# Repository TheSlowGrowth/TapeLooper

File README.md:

# TapeLooper

A digital tape looper module for Eurorack or standalone use, built on the [Daisy Seed](https://electro-smith.com/product/daisy-seed/).

## Features

- **4 stereo or mono tape loop channels** - record and play back independent, unsynchronized tape loops
- **Motor simulation** - playback speed ramps up and down with a configurable rate
- **Tape simulation** - with drive, grain and warble independently controllable
- **Variable playback speed** - with Volt/Octave CV control and quarter/half/double/quad speed
- **Forward and reverse playback**
- **Amplitude CV control**
- **Clean recording** — audio records cleanly into loop channels; tape simulation is applied during playback only
- **Perfect loop recording** - with a small crossfade at the loop point
- **SD card storage** - save and load loops as 48kHz stereo WAV files

## Hardware

Based on the Electrosmith Daisy Seed. Designed to operate as either a Eurorack module or a standalone desktop unit.

## Project Structure

- `dsp/` — DSP library: audio processing, loop playback/recording, tape simulation
- `firmware/` — Target firmware: main application, UI, SD card I/O
- `hardware/` — KiCad PCB designs and panel artwork
- `lib/` — External dependencies
- `scripts/` — Development helper scripts

## Development

### Requirements

- **CMake** 3.30+
- **clang++** (C++17) for building and running unit tests
- **arm-none-eabi-gcc** 10-2020-q4 recommended for cross-compiling firmware to the Daisy Seed
- **Python 3** with `pip` (for pre-commit hooks)

### Unit Tests

Tests are written with Google Test. Build and run from the respective `tests/` directories:

```bash
# DSP library tests
cd dsp/tests && make test

# Firmware tests
cd firmware/tests && make test
```

### Pre-commit Hook

A pre-commit hook runs `clang-format` on staged files before each commit. To install:

```bash
./scripts/setup-clangformat-precommit-hook.sh
```

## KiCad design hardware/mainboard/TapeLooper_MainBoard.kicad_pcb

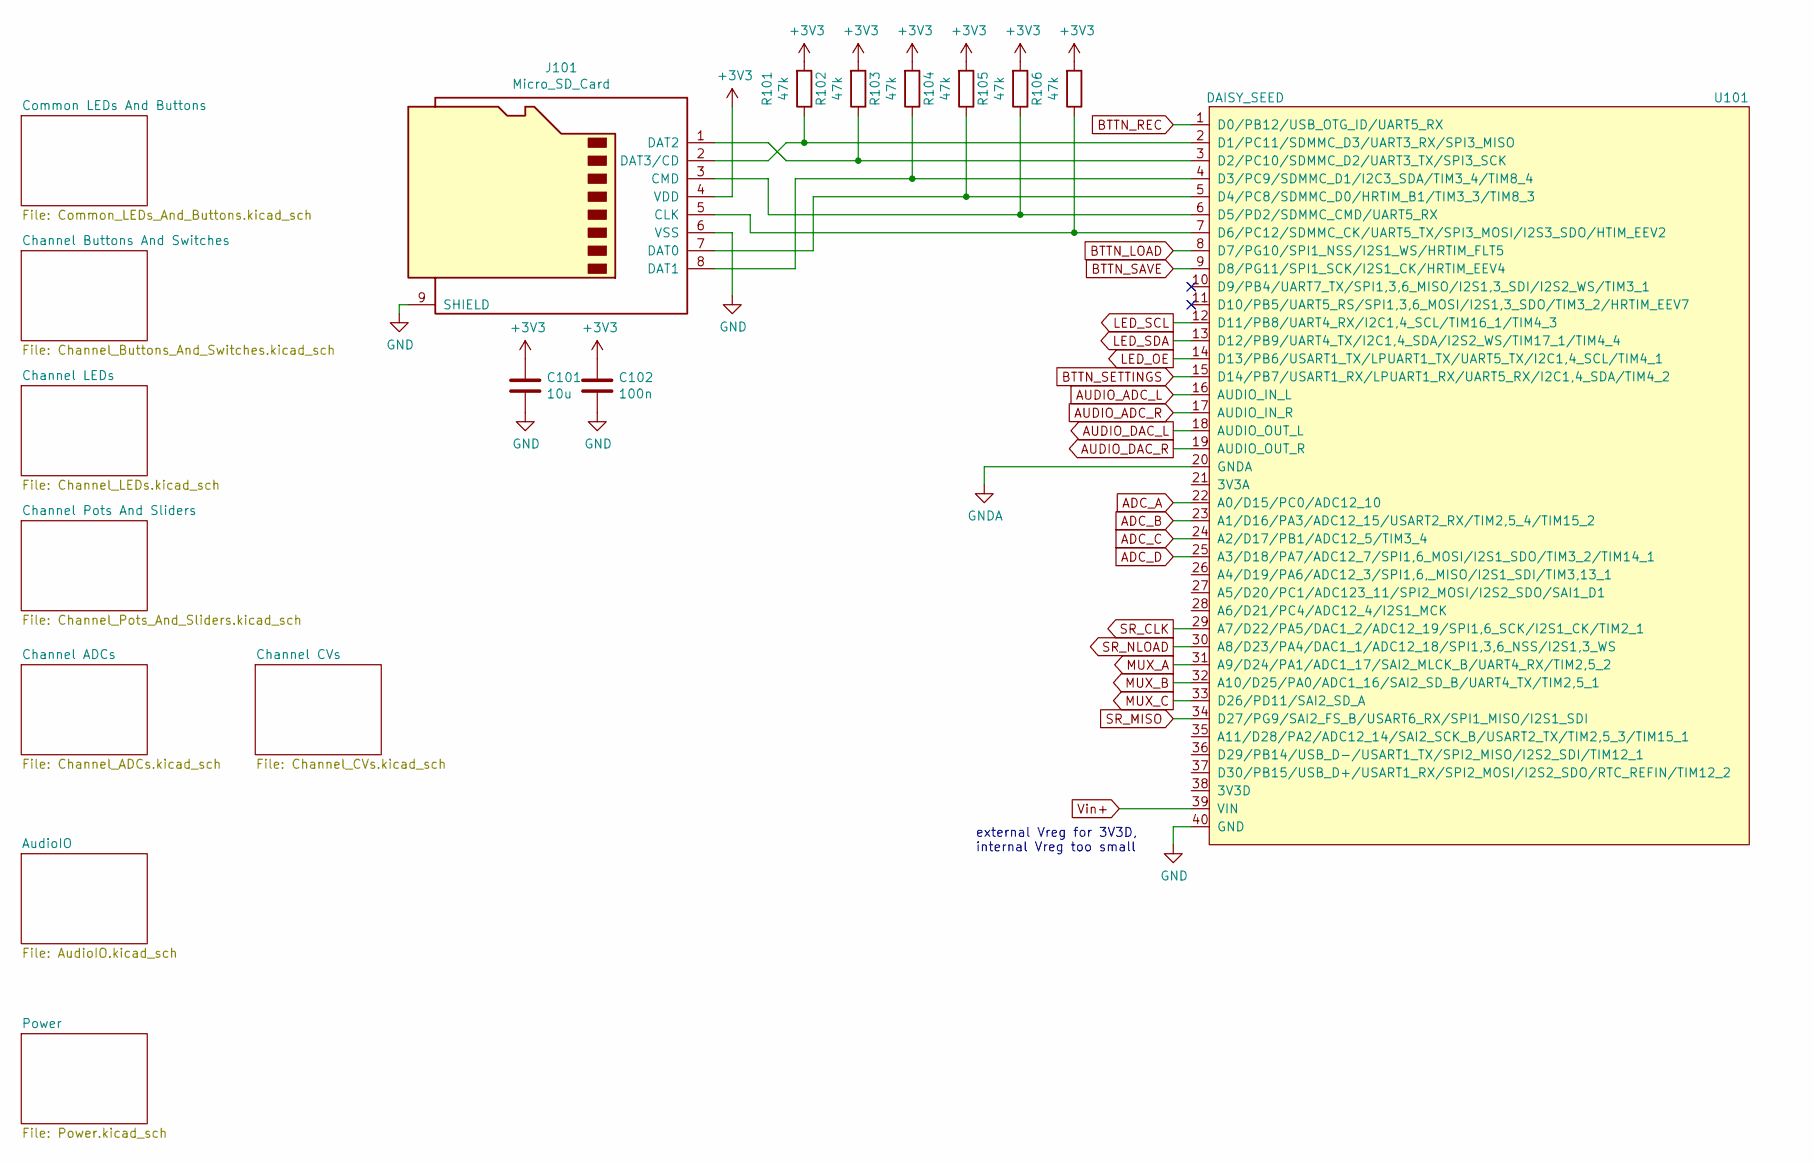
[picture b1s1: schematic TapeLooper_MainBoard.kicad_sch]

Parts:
C101: 10u; C_0603_1608Metric_Pad1.08x0.95mm_HandSolder
C102: 100n; C_0603_1608Metric_Pad1.08x0.95mm_HandSolder
J101: Micro_SD_Card; PJS008U-3000
R101, R102, R103, R104, R105, R106: 47k; R_0603_1608Metric_Pad0.98x0.95mm_HandSolder
U101: DAISY_SEED; Daisy_Seed

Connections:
ADC_A: U101.22 (A0/D15/PC0/ADC12_10); also elsewhere on the board
ADC_B: U101.23 (A1/D16/PA3/ADC12_15/USART2_RX/TIM2,5_4/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); also elsewhere on the board
ADC_C: U101.24 (A2/D17/PB1/ADC12_5/TIM3_4); also elsewhere on the board
ADC_D: U101.25 (A3/D18/PA7/ADC12_7/SPI1,6_MOSI/I2S1_SDO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); also elsewhere on the board
AUDIO_ADC_L: U101.16 (AUDIO_IN_L); also elsewhere on the board
AUDIO_ADC_R: U101.17 (AUDIO_IN_R); also elsewhere on the board
AUDIO_DAC_L: U101.18 (AUDIO_OUT_L); also elsewhere on the board
AUDIO_DAC_R: U101.19 (AUDIO_OUT_R); also elsewhere on the board
BTTN_LOAD: U101.8 (D7/PG10/SPI1_NSS/I2S1_WS/HRTIM_FLT5); also elsewhere on the board
BTTN_REC: U101.1 (D0/PB12/USB_OTG_ID/UART5_RX); also elsewhere on the board
BTTN_SAVE: U101.9 (D8/PG11/SPI1_SCK/I2S1_CK/HRTIM_EEV4); also elsewhere on the board
BTTN_SETTINGS: U101.15 (D14/PB7/USART1_RX/LPUART1_RX/UART5_RX/I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); also elsewhere on the board
GND: C101.2, C102.2, J101.6 (VSS), J101.9 (SHIELD), U101.40 (GND); also elsewhere on the board
LED_OE: U101.14 (D13/PB6/USART1_TX/LPUART1_TX/UART5_TX/I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); also elsewhere on the board
LED_SCL: U101.12 (D11/PB8/UART4_RX/I2C1,4_SCL/TIM16_1/TIM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); also elsewhere on the board
LED_SDA: U101.13 (D12/PB9/UART4_TX/I2C1,4_SDA/I2S2_WS/TIM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); also elsewhere on the board
MUX_A: U101.31 (A9/D24/PA1/ADC1_17/SAI2_MLCK_B/UART4_RX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); also elsewhere on the board
MUX_B: U101.32 (A10/D25/PA0/ADC1_16/SAI2_SD_B/UART4_TX/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); also elsewhere on the board
MUX_C: U101.33 (D26/PD11/SAI2_SD_A); also elsewhere on the board
unnamed: J101.5 (CLK), R106.1, U101.7 (D6/PC12/SDMMC_CK/UART5_TX/SPI3_MOSI/I2S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)
unnamed: J101.3 (CMD), R105.1, U101.6 (D5/PD2/SDMMC_CMD/UART5_RX)
unnamed: J101.7 (DAT0), R104.1, U101.5 (D4/PC8/SDMMC_D0/HRTIM_B1/TIM3_3/TIM8_3)
unnamed: J101.8 (DAT1), R103.1, U101.4 (D3/PC9/SDMMC_D1/I2C3_SDA/TIM3_4/TIM8_4)
unnamed: J101.1 (DAT2), R102.1, U101.3 (D2/PC10/SDMMC_D2/UART3_TX/SPI3_SCK)
unnamed: J101.2 (DAT3/CD), R101.1, U101.2 (D1/PC11/SDMMC_D3/UART3_RX/SPI3_MISO)
SR_CLK: U101.29 (A7/D22/PA5/DAC1_2/ADC12_19/SPI1,6_SCK/I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); also elsewhere on the board
SR_MISO: U101.34 (D27/PG9/SAI2_FS_B/USART6_RX/SPI1_MISO/I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); also elsewhere on the board
SR_NLOAD: U101.30 (A8/D23/PA4/DAC1_1/ADC12_18/SPI1,3,6_NSS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); also elsewhere on the board
Vin+: U101.39 (VIN); also elsewhere on the board

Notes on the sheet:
external Vreg for 3V3D, internal Vreg too small

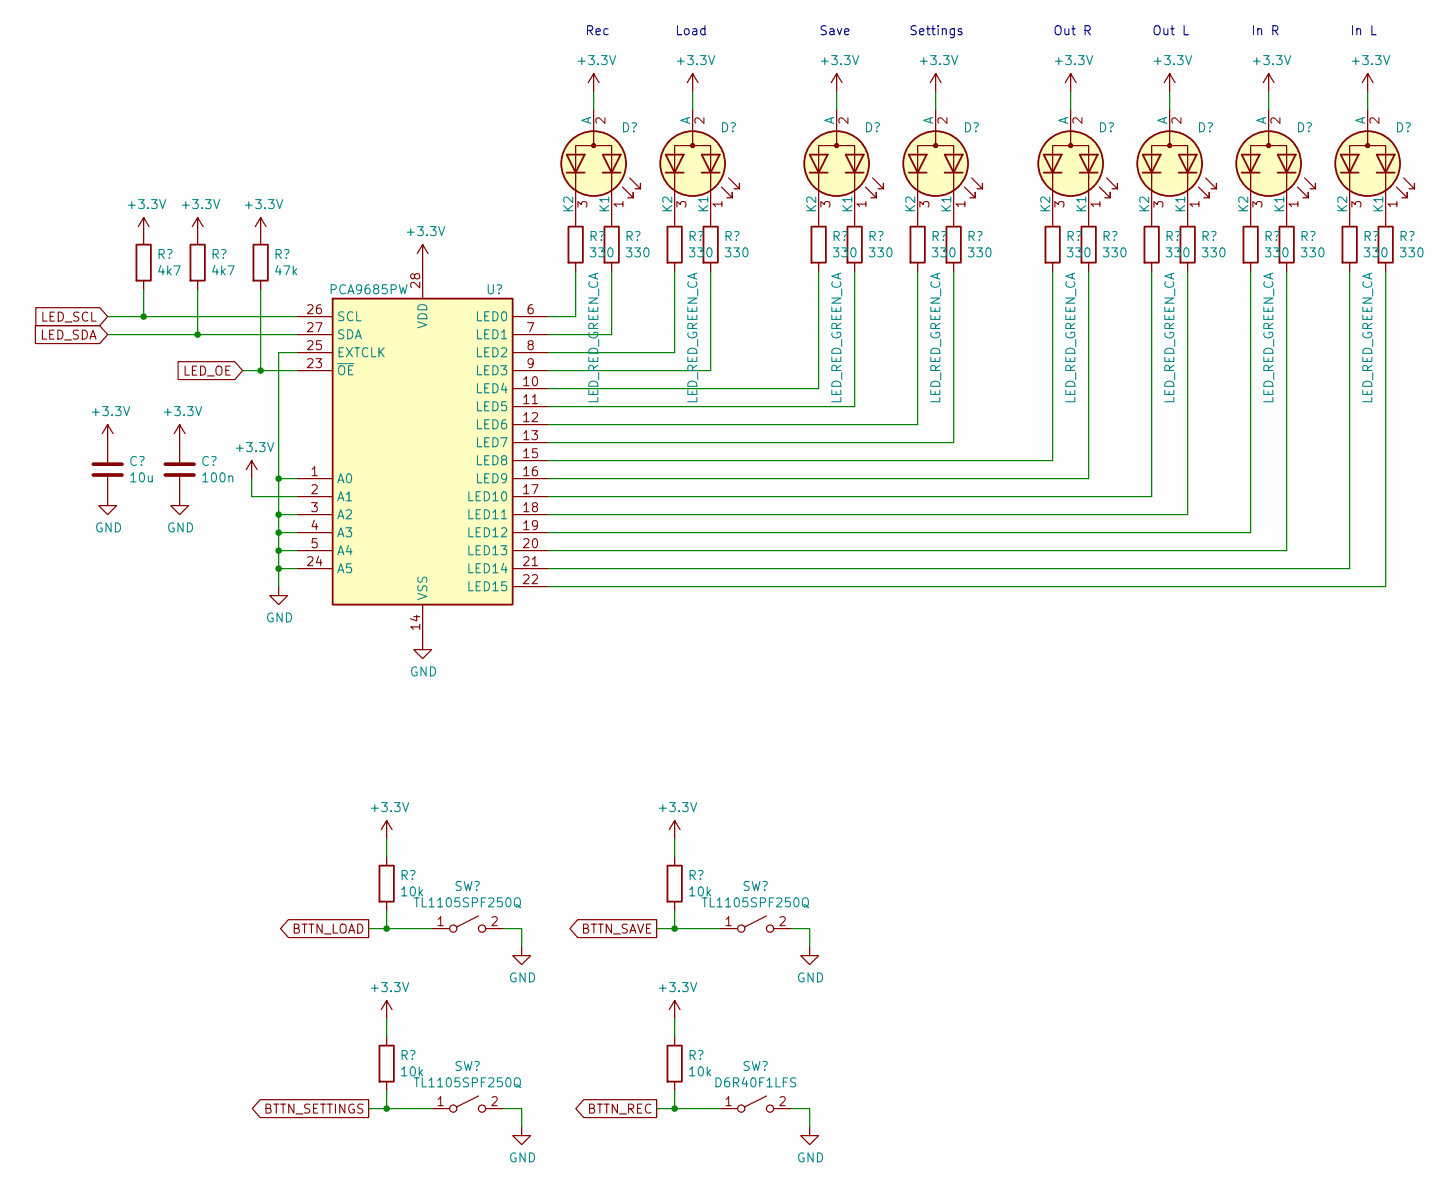
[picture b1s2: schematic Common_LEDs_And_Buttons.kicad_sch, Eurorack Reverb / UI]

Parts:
C201: 10u; C_0603_1608Metric_Pad1.08x0.95mm_HandSolder
C202: 100n; C_0603_1608Metric_Pad1.08x0.95mm_HandSolder
D201, D202, D203, D204, D205, D206, D207, D208: LED_RED_GREEN_CA; LED_D3.0mm-3
R201, R202, R203, R204, R205, R206, R207, R208, R209, R210, R211, R212, R213, R214, R215, R216: 330; R_0603_1608Metric_Pad0.98x0.95mm_HandSolder
R217, R218: 4k7; R_0603_1608Metric_Pad0.98x0.95mm_HandSolder
R219: 47k; R_0603_1608Metric_Pad0.98x0.95mm_HandSolder
R220, R221, R222, R223: 10k; R_0603_1608Metric_Pad0.98x0.95mm_HandSolder
SW201, SW202, SW203: TL1105SPF250Q; SW_PUSH_6mm
SW204: D6R40F1LFS; CK-D6R_Pushbutton
U201: PCA9685PW; TSSOP-28_4.4x9.7mm_P0.65mm

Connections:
BTTN_LOAD: R220.2, SW201.1 (A); also elsewhere on the board
BTTN_REC: R223.2, SW204.1 (A); also elsewhere on the board
BTTN_SAVE: R221.2, SW202.1 (A); also elsewhere on the board
BTTN_SETTINGS: R222.2, SW203.1 (A); also elsewhere on the board
GND: C201.2, C202.2, SW201.2 (B), SW202.2 (B), SW203.2 (B), SW204.2 (B), U201.1 (A0), U201.3 (A2), U201.4 (A3), U201.5 (A4), U201.14 (VSS), U201.24 (A5), U201.25 (EXTCLK); also elsewhere on the board
LED_OE: R219.2, U201.23 (~OE); also elsewhere on the board
LED_SCL: R217.2, U201.26 (SCL); also elsewhere on the board
LED_SDA: R218.2, U201.27 (SDA); also elsewhere on the board
unnamed: D201.1 (K1), R202.1
unnamed: D201.3 (K2), R201.1
unnamed: D202.1 (K1), R204.1
unnamed: D202.3 (K2), R203.1
unnamed: D203.1 (K1), R206.1
unnamed: D203.3 (K2), R205.1
unnamed: D204.1 (K1), R208.1
unnamed: D204.3 (K2), R207.1
unnamed: D205.1 (K1), R210.1
unnamed: D205.3 (K2), R209.1
unnamed: D206.1 (K1), R212.1
unnamed: D206.3 (K2), R211.1
unnamed: D207.1 (K1), R214.1
unnamed: D207.3 (K2), R213.1
unnamed: D208.1 (K1), R216.1
unnamed: D208.3 (K2), R215.1
unnamed: R201.2, U201.6 (LED0)
unnamed: R202.2, U201.7 (LED1)
unnamed: R203.2, U201.8 (LED2)
unnamed: R204.2, U201.9 (LED3)
unnamed: R205.2, U201.10 (LED4)
unnamed: R206.2, U201.11 (LED5)
unnamed: R207.2, U201.12 (LED6)
unnamed: R208.2, U201.13 (LED7)
unnamed: R209.2, U201.15 (LED8)
unnamed: R210.2, U201.16 (LED9)
unnamed: R211.2, U201.17 (LED10)
unnamed: R212.2, U201.18 (LED11)
unnamed: R213.2, U201.19 (LED12)
unnamed: R214.2, U201.20 (LED13)
unnamed: R215.2, U201.21 (LED14)
unnamed: R216.2, U201.22 (LED15)

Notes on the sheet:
In R
Rec
Load
Out L
In L
Settings
Save
Out R

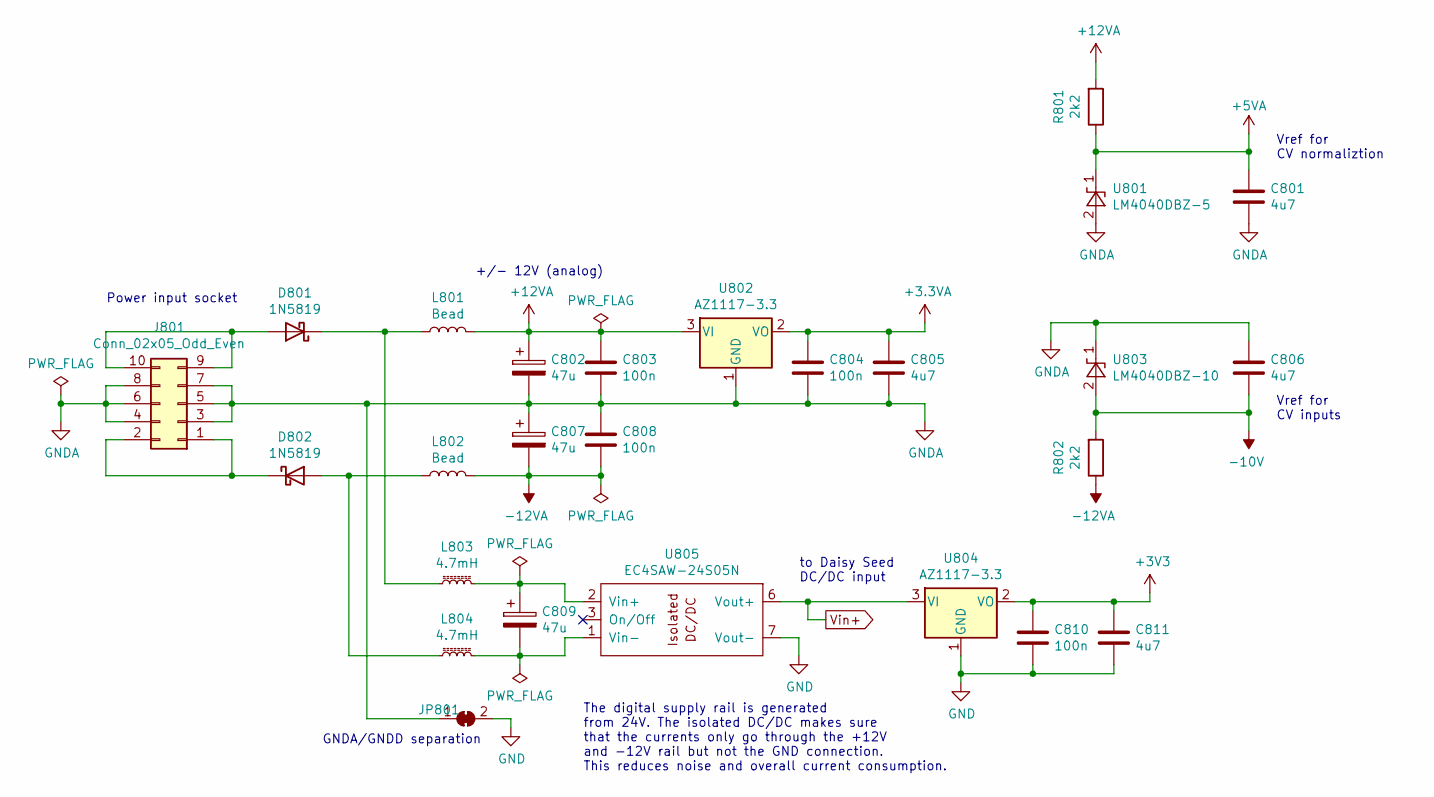
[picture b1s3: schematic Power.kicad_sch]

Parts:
C801, C805, C806, C811: 4u7; C_0603_1608Metric_Pad1.08x0.95mm_HandSolder
C802, C807, C809: 47u; CP_Elec_6.3x5.8
C803, C804, C808, C810: 100n; C_0603_1608Metric_Pad1.08x0.95mm_HandSolder
D801, D802: 1N5819; D_SOD-123
J801: Conn_02x05_Odd_Even; IDC-Header_2x05_P2.54mm_Vertical
JP801: SolderJumper_2_Bridged; SolderJumper-2_P1.3mm_Bridged2Bar_RoundedPad1.0x1.5mm
L801, L802: Bead; L_0603_1608Metric_Pad1.05x0.95mm_HandSolder
L803, L804: 4.7mH; L_1210_3225Metric_Pad1.42x2.65mm_HandSolder
R801, R802: 2k2; R_0603_1608Metric_Pad0.98x0.95mm_HandSolder
U801: LM4040DBZ-5; SOT-23
U802, U804: AZ1117-3.3; SOT-223-3_TabPin2
U803: LM4040DBZ-10; SOT-23
U805: EC4SAW-24S05N; EC4SAW_DC_DC_SIP8

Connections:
+5VA: C801.1, R801.1, U801.1 (K); also elsewhere on the board
+12VA: C802.1, C803.1, L801.2, R801.2, U802.3 (VI); also elsewhere on the board
-10V: C806.2, R802.2, U803.2 (A); also elsewhere on the board
-12VA: C807.2, C808.2, L802.2, R802.1; also elsewhere on the board
GND: C810.2, C811.2, JP801.2 (B), U804.1 (GND), U805.7 (Vout-); also elsewhere on the board
unnamed: D801.2 (A), J801.9, J801.10
unnamed: D801.1 (K), L801.1, L803.1
unnamed: D802.2 (A), L802.1, L804.1
unnamed: D802.1 (K), J801.1, J801.2
unnamed: C809.1, L803.2, U805.2 (Vin+)
unnamed: C809.2, L804.2, U805.1 (Vin-)
Vin+: U804.3 (VI), U805.6 (Vout+); also elsewhere on the board

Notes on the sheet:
GNDA/GNDD separation
to Daisy Seed DC/DC input
The digital supply rail is generated from 24V. The isolated DC/DC makes sure that the currents only go through the +12V and -12V rail but not the GND connection. This reduces noise and overall current consumption.
Power input socket
Vref for CV normaliztion
+/- 12V (analog)
Vref for CV inputs

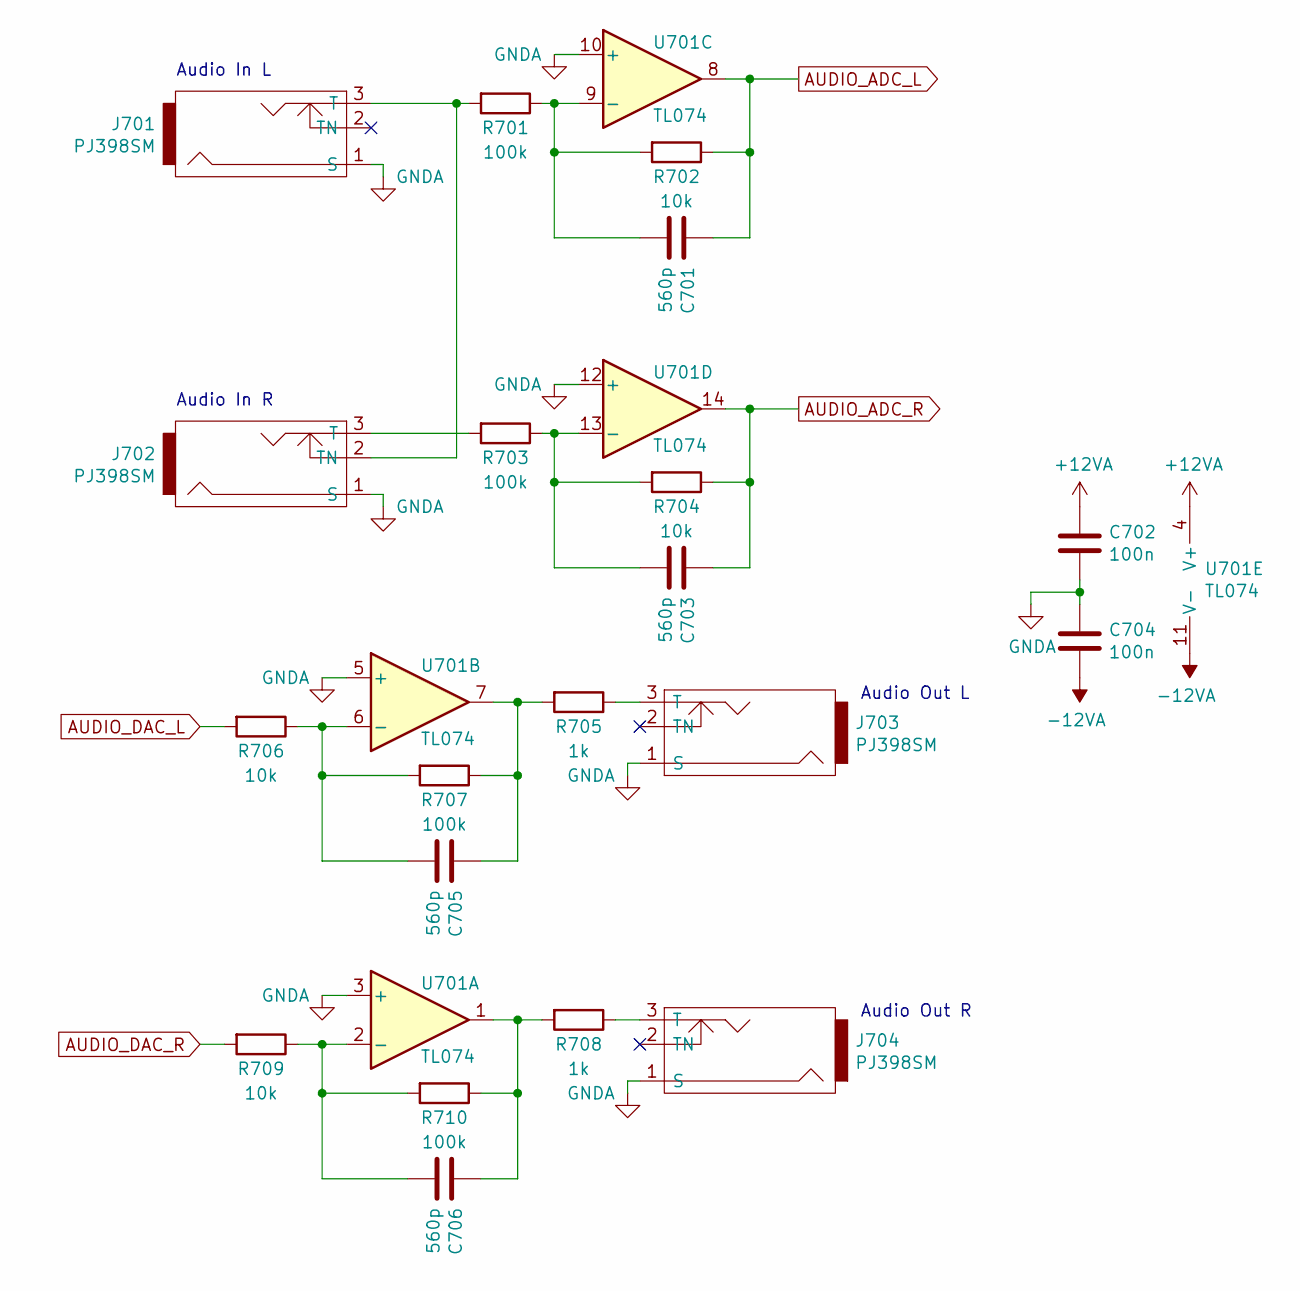
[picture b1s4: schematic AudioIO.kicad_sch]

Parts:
C701, C703, C705, C706: 560p; C_0603_1608Metric_Pad1.08x0.95mm_HandSolder
C702, C704: 100n; C_0603_1608Metric_Pad1.08x0.95mm_HandSolder
J701, J702, J703, J704: PJ398SM; THONKICONN
R701, R703, R707, R710: 100k; R_0603_1608Metric_Pad0.98x0.95mm_HandSolder
R702, R704, R706, R709: 10k; R_0603_1608Metric_Pad0.98x0.95mm_HandSolder
R705, R708: 1k; R_0603_1608Metric_Pad0.98x0.95mm_HandSolder
U701: TL074; SOIC-14_3.9x8.7mm_P1.27mm

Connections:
+12VA: C702.1, U701.4 (V+); also elsewhere on the board
-12VA: C704.2, U701.11 (V-); also elsewhere on the board
AUDIO_ADC_L: C701.1, R702.1, U701.8; also elsewhere on the board
AUDIO_ADC_R: C703.1, R704.1, U701.14; also elsewhere on the board
AUDIO_DAC_L: R706.2; also elsewhere on the board
AUDIO_DAC_R: R709.2; also elsewhere on the board
unnamed: C705.1, R705.2, R707.1, U701.7
unnamed: C706.1, R708.2, R710.1, U701.1
unnamed: J701.3 (T), J702.2 (TN), R701.2
unnamed: J702.3 (T), R703.2
unnamed: J703.3 (T), R705.1
unnamed: J704.3 (T), R708.1
unnamed: C706.2, R709.1, R710.2, U701.2 (-)
unnamed: C705.2, R706.1, R707.2, U701.6 (-)
unnamed: C701.2, R701.1, R702.2, U701.9 (-)
unnamed: C703.2, R703.1, R704.2, U701.13 (-)

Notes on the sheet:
Audio Out L
Audio In L
Audio In R
Audio Out R

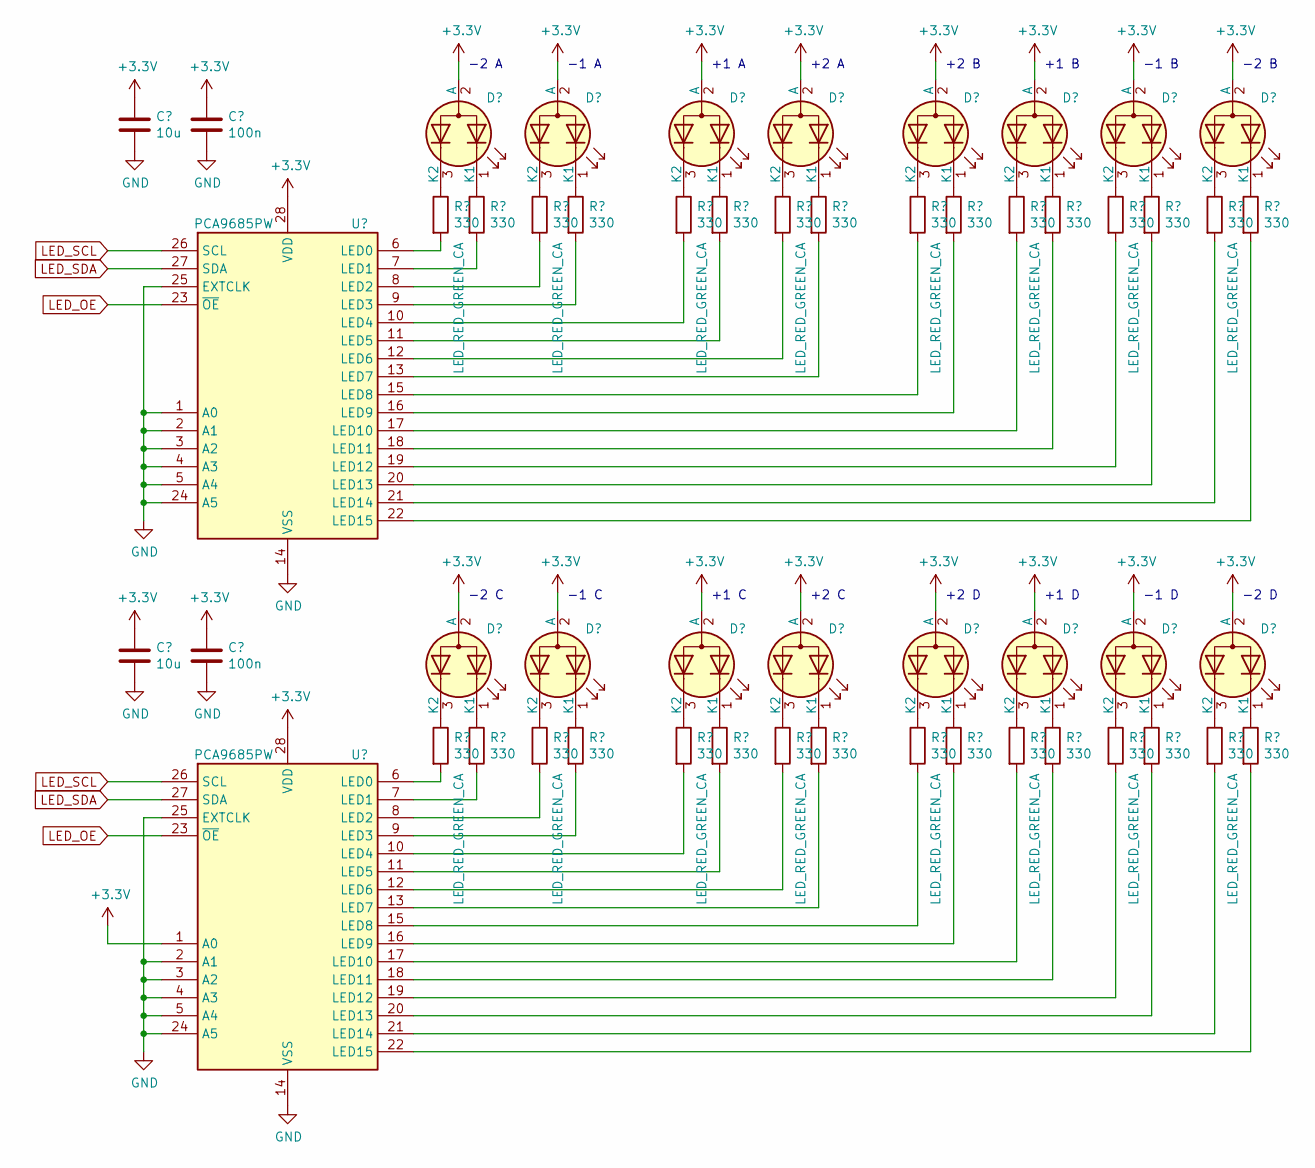
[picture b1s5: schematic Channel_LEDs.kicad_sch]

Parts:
C401, C403: 10u; C_0603_1608Metric_Pad1.08x0.95mm_HandSolder
C402, C404: 100n; C_0603_1608Metric_Pad1.08x0.95mm_HandSolder
D401, D402, D403, D404, D405, D406, D407, D408, D409, D410, D411, D412, D413, D414, D415, D416: LED_RED_GREEN_CA; LED_D3.0mm-3
R401, R402, R403, R404, R405, R406, R407, R408, R409, R410, R411, R412, R413, R414, R415, R416, R417, R418, R419, R420, R421, R422, R423, R424, R425, R426, R427, R428, R429, R430, R431, R432: 330; R_0603_1608Metric_Pad0.98x0.95mm_HandSolder
U401, U402: PCA9685PW; TSSOP-28_4.4x9.7mm_P0.65mm

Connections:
GND: C401.2, C402.2, C403.2, C404.2, U401.1 (A0), U401.2 (A1), U401.3 (A2), U401.4 (A3), U401.5 (A4), U401.14 (VSS), U401.24 (A5), U401.25 (EXTCLK), U402.2 (A1), U402.3 (A2), U402.4 (A3), U402.5 (A4), U402.14 (VSS), U402.24 (A5), U402.25 (EXTCLK); also elsewhere on the board
LED_OE: U401.23 (~OE), U402.23 (~OE); also elsewhere on the board
LED_SCL: U401.26 (SCL), U402.26 (SCL); also elsewhere on the board
LED_SDA: U401.27 (SDA), U402.27 (SDA); also elsewhere on the board
unnamed: D401.1 (K1), R402.1
unnamed: D401.3 (K2), R401.1
unnamed: D402.1 (K1), R404.1
unnamed: D402.3 (K2), R403.1
unnamed: D403.1 (K1), R406.1
unnamed: D403.3 (K2), R405.1
unnamed: D404.1 (K1), R408.1
unnamed: D404.3 (K2), R407.1
unnamed: D405.1 (K1), R410.1
unnamed: D405.3 (K2), R409.1
unnamed: D406.1 (K1), R412.1
unnamed: D406.3 (K2), R411.1
unnamed: D407.1 (K1), R414.1
unnamed: D407.3 (K2), R413.1
unnamed: D408.1 (K1), R416.1
unnamed: D408.3 (K2), R415.1
unnamed: D409.1 (K1), R418.1
unnamed: D409.3 (K2), R417.1
unnamed: D410.1 (K1), R420.1
unnamed: D410.3 (K2), R419.1
unnamed: D411.1 (K1), R422.1
unnamed: D411.3 (K2), R421.1
unnamed: D412.1 (K1), R424.1
unnamed: D412.3 (K2), R423.1
unnamed: D413.1 (K1), R426.1
unnamed: D413.3 (K2), R425.1
unnamed: D414.1 (K1), R428.1
unnamed: D414.3 (K2), R427.1
unnamed: D415.1 (K1), R430.1
unnamed: D415.3 (K2), R429.1
unnamed: D416.1 (K1), R432.1
unnamed: D416.3 (K2), R431.1
unnamed: R401.2, U401.6 (LED0)
unnamed: R402.2, U401.7 (LED1)
unnamed: R403.2, U401.8 (LED2)
unnamed: R404.2, U401.9 (LED3)
unnamed: R405.2, U401.10 (LED4)
unnamed: R406.2, U401.11 (LED5)
unnamed: R407.2, U401.12 (LED6)
unnamed: R408.2, U401.13 (LED7)
unnamed: R409.2, U401.15 (LED8)
unnamed: R410.2, U401.16 (LED9)
unnamed: R411.2, U401.17 (LED10)
unnamed: R412.2, U401.18 (LED11)
unnamed: R413.2, U401.19 (LED12)
unnamed: R414.2, U401.20 (LED13)
unnamed: R415.2, U401.21 (LED14)
unnamed: R416.2, U401.22 (LED15)
unnamed: R417.2, U402.6 (LED0)
unnamed: R418.2, U402.7 (LED1)
unnamed: R419.2, U402.8 (LED2)
unnamed: R420.2, U402.9 (LED3)
unnamed: R421.2, U402.10 (LED4)
unnamed: R422.2, U402.11 (LED5)
unnamed: R423.2, U402.12 (LED6)
unnamed: R424.2, U402.13 (LED7)
unnamed: R425.2, U402.15 (LED8)
unnamed: R426.2, U402.16 (LED9)
unnamed: R427.2, U402.17 (LED10)
unnamed: R428.2, U402.18 (LED11)
unnamed: R429.2, U402.19 (LED12)
unnamed: R430.2, U402.20 (LED13)
unnamed: R431.2, U402.21 (LED14)
unnamed: R432.2, U402.22 (LED15)

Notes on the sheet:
-2 A
+2 B
+1 A
-1 B
-2 C
-2 D
-1 A
-2 B
+2 C
+2 D
+1 D
+1 C
+2 A
+1 B
-1 C
-1 D

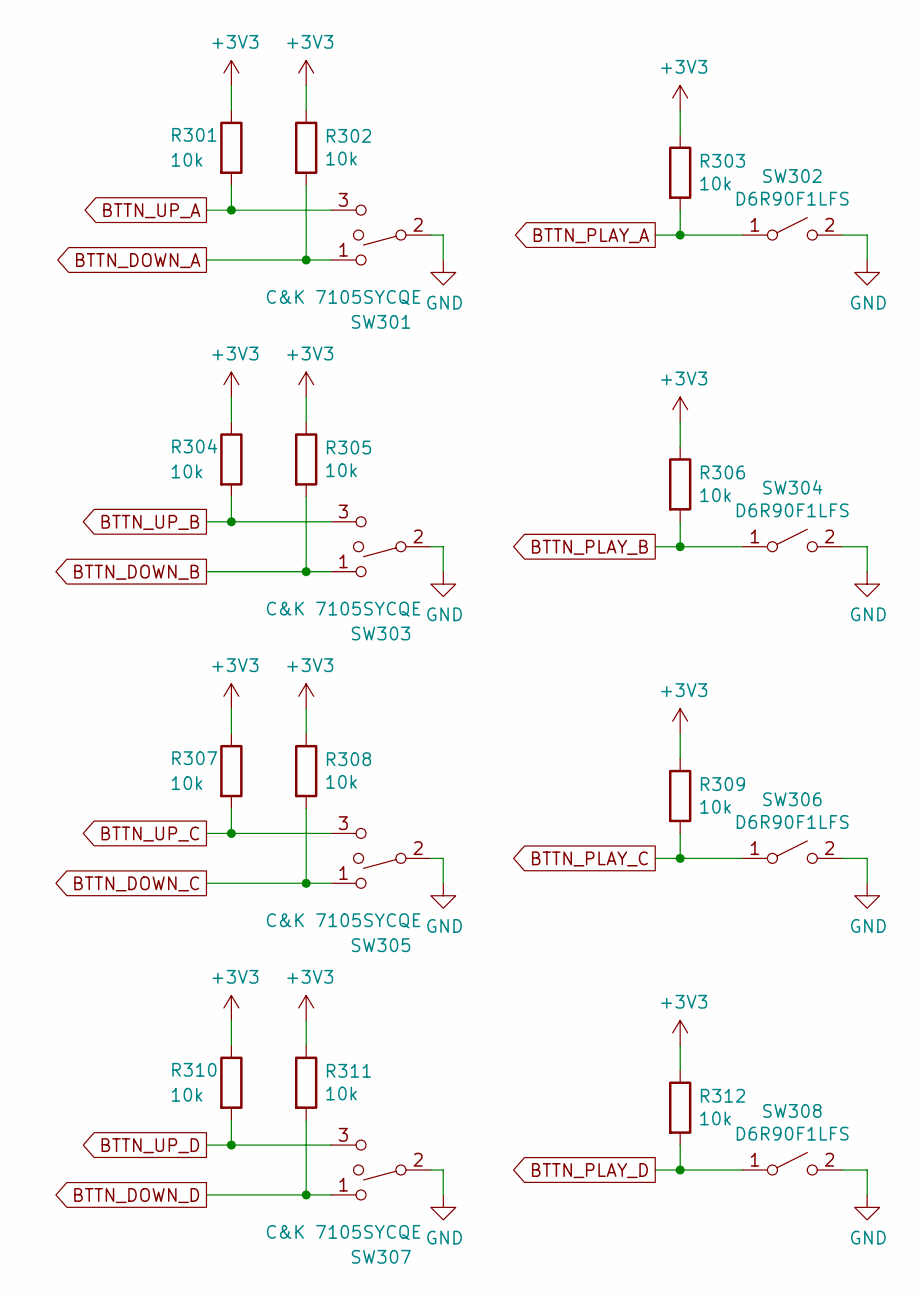
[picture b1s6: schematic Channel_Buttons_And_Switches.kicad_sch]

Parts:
R301, R302, R303, R304, R305, R306, R307, R308, R309, R310, R311, R312: 10k; R_0603_1608Metric_Pad0.98x0.95mm_HandSolder
SW301, SW303, SW305, SW307: C&K 7105SYCQE; 7105SYCQE-1P3T-SP3T-Switch
SW302, SW304, SW306, SW308: D6R90F1LFS; CK-D6R_Pushbutton

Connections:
BTTN_DOWN_A: R302.2, SW301.1; also elsewhere on the board
BTTN_DOWN_B: R305.2, SW303.1; also elsewhere on the board
BTTN_DOWN_C: R308.2, SW305.1; also elsewhere on the board
BTTN_DOWN_D: R311.2, SW307.1; also elsewhere on the board
BTTN_PLAY_A: R303.2, SW302.1 (A); also elsewhere on the board
BTTN_PLAY_B: R306.2, SW304.1 (A); also elsewhere on the board
BTTN_PLAY_C: R309.2, SW306.1 (A); also elsewhere on the board
BTTN_PLAY_D: R312.2, SW308.1 (A); also elsewhere on the board
BTTN_UP_A: R301.2, SW301.3; also elsewhere on the board
BTTN_UP_B: R304.2, SW303.3; also elsewhere on the board
BTTN_UP_C: R307.2, SW305.3; also elsewhere on the board
BTTN_UP_D: R310.2, SW307.3; also elsewhere on the board
GND: SW301.2, SW302.2 (B), SW303.2, SW304.2 (B), SW305.2, SW306.2 (B), SW307.2, SW308.2 (B); also elsewhere on the board

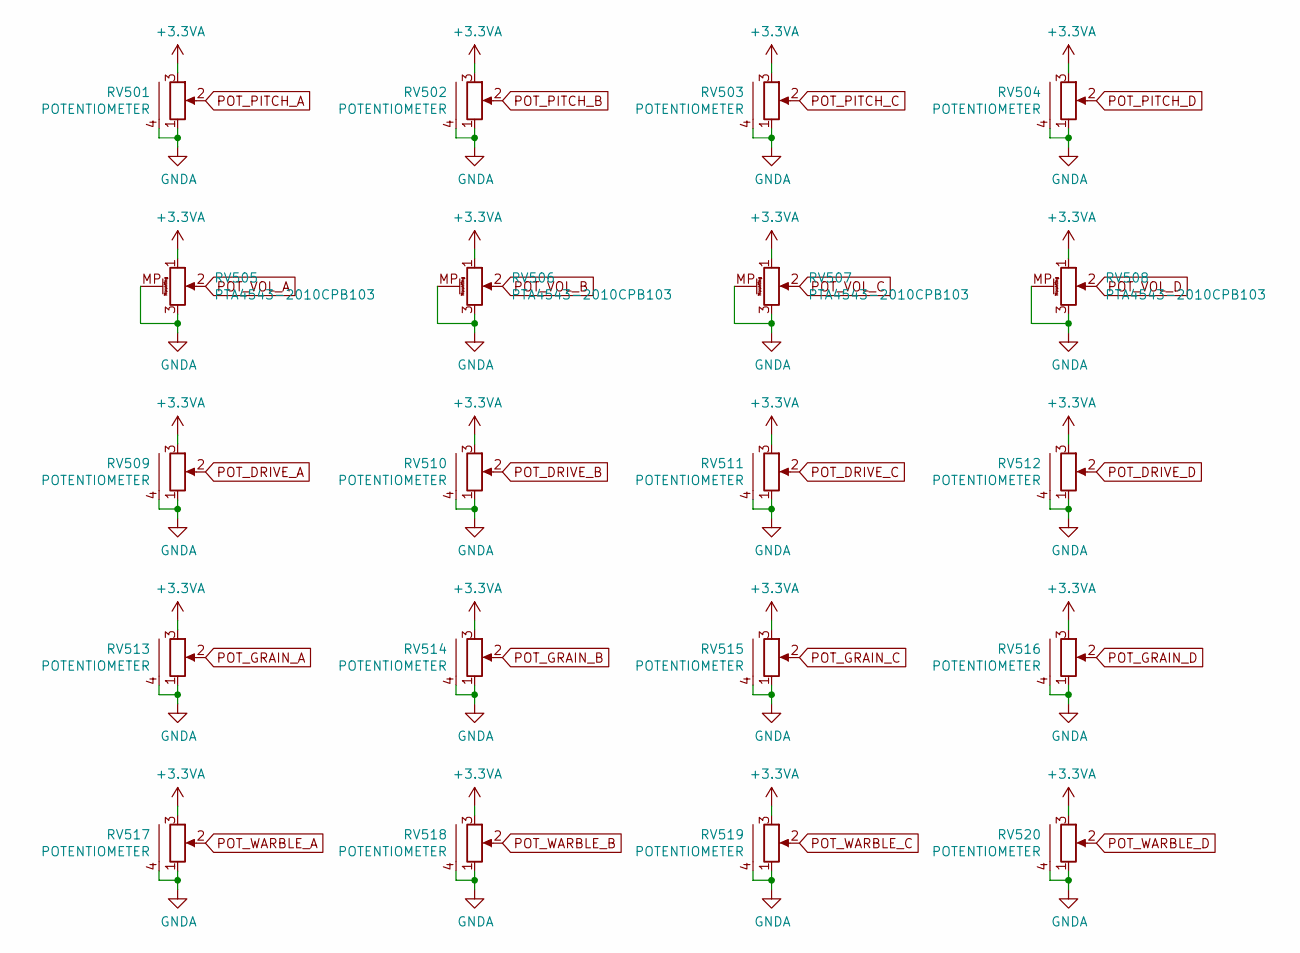
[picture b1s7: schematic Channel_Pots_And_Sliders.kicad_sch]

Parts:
RV501, RV502, RV503, RV504, RV509, RV510, RV511, RV512, RV513, RV514, RV515, RV516, RV517, RV518, RV519, RV520: POTENTIOMETER; 9mm_pot
RV505, RV506, RV507, RV508: PTA4543-2010CPB103; Potentiometer_Bourns_PTA4543_Single_Slide

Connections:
POT_DRIVE_A: RV509.2 (wiper); also elsewhere on the board
POT_DRIVE_B: RV510.2 (wiper); also elsewhere on the board
POT_DRIVE_C: RV511.2 (wiper); also elsewhere on the board
POT_DRIVE_D: RV512.2 (wiper); also elsewhere on the board
POT_GRAIN_A: RV513.2 (wiper); also elsewhere on the board
POT_GRAIN_B: RV514.2 (wiper); also elsewhere on the board
POT_GRAIN_C: RV515.2 (wiper); also elsewhere on the board
POT_GRAIN_D: RV516.2 (wiper); also elsewhere on the board
POT_PITCH_A: RV501.2 (wiper); also elsewhere on the board
POT_PITCH_B: RV502.2 (wiper); also elsewhere on the board
POT_PITCH_C: RV503.2 (wiper); also elsewhere on the board
POT_PITCH_D: RV504.2 (wiper); also elsewhere on the board
POT_VOL_A: RV505.2; also elsewhere on the board
POT_VOL_B: RV506.2; also elsewhere on the board
POT_VOL_C: RV507.2; also elsewhere on the board
POT_VOL_D: RV508.2; also elsewhere on the board
POT_WARBLE_A: RV517.2 (wiper); also elsewhere on the board
POT_WARBLE_B: RV518.2 (wiper); also elsewhere on the board
POT_WARBLE_C: RV519.2 (wiper); also elsewhere on the board
POT_WARBLE_D: RV520.2 (wiper); also elsewhere on the board

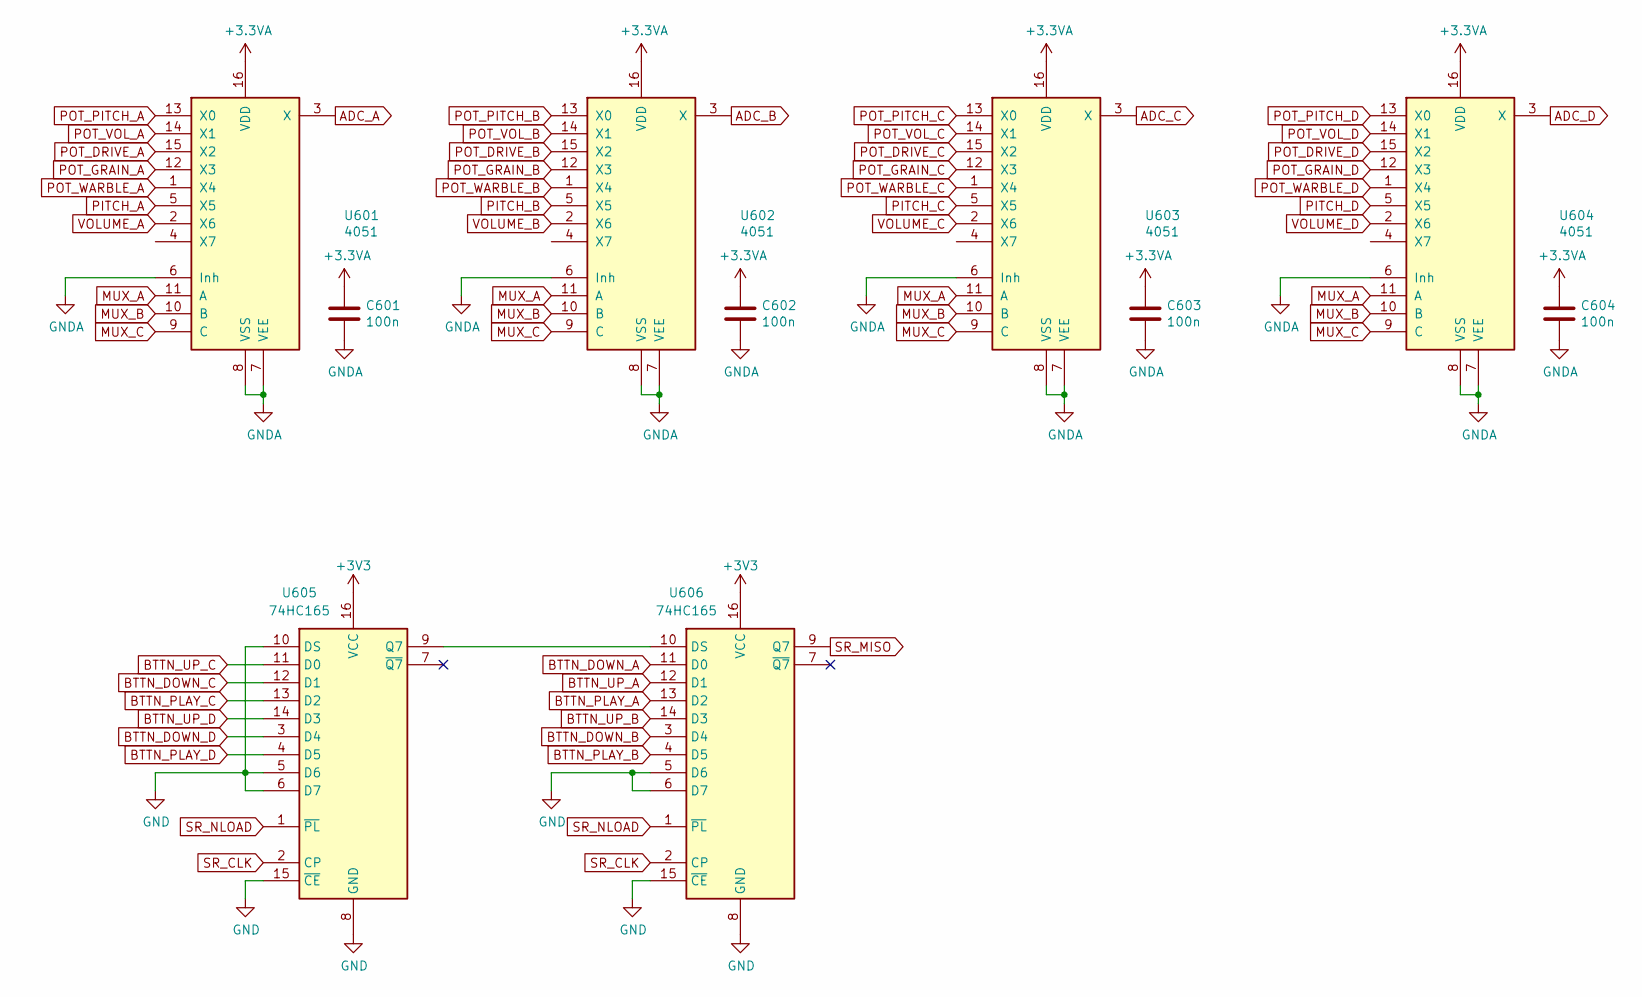
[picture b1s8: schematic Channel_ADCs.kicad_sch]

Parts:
C601, C602, C603, C604: 100n; C_0603_1608Metric_Pad1.08x0.95mm_HandSolder
U601, U602, U603, U604: 4051; SO-16_3.9x9.9mm_P1.27mm
U605, U606: 74HC165; SO-16_3.9x9.9mm_P1.27mm

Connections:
ADC_A: U601.3 (X); also elsewhere on the board
ADC_B: U602.3 (X); also elsewhere on the board
ADC_C: U603.3 (X); also elsewhere on the board
ADC_D: U604.3 (X); also elsewhere on the board
BTTN_DOWN_A: U606.11 (D0); also elsewhere on the board
BTTN_DOWN_B: U606.3 (D4); also elsewhere on the board
BTTN_DOWN_C: U605.12 (D1); also elsewhere on the board
BTTN_DOWN_D: U605.3 (D4); also elsewhere on the board
BTTN_PLAY_A: U606.13 (D2); also elsewhere on the board
BTTN_PLAY_B: U606.4 (D5); also elsewhere on the board
BTTN_PLAY_C: U605.13 (D2); also elsewhere on the board
BTTN_PLAY_D: U605.4 (D5); also elsewhere on the board
BTTN_UP_A: U606.12 (D1); also elsewhere on the board
BTTN_UP_B: U606.14 (D3); also elsewhere on the board
BTTN_UP_C: U605.11 (D0); also elsewhere on the board
BTTN_UP_D: U605.14 (D3); also elsewhere on the board
GND: U605.5 (D6), U605.6 (D7), U605.8 (GND), U605.10 (DS), U605.15 (~CE), U606.5 (D6), U606.6 (D7), U606.8 (GND), U606.15 (~CE); also elsewhere on the board
MUX_A: U601.11 (A), U602.11 (A), U603.11 (A), U604.11 (A); also elsewhere on the board
MUX_B: U601.10 (B), U602.10 (B), U603.10 (B), U604.10 (B); also elsewhere on the board
MUX_C: U601.9 (C), U602.9 (C), U603.9 (C), U604.9 (C); also elsewhere on the board
unnamed: U605.9 (Q7), U606.10 (DS)
PITCH_A: U601.5 (X5); also elsewhere on the board
PITCH_B: U602.5 (X5); also elsewhere on the board
PITCH_C: U603.5 (X5); also elsewhere on the board
PITCH_D: U604.5 (X5); also elsewhere on the board
POT_DRIVE_A: U601.15 (X2); also elsewhere on the board
POT_DRIVE_B: U602.15 (X2); also elsewhere on the board
POT_DRIVE_C: U603.15 (X2); also elsewhere on the board
POT_DRIVE_D: U604.15 (X2); also elsewhere on the board
POT_GRAIN_A: U601.12 (X3); also elsewhere on the board
POT_GRAIN_B: U602.12 (X3); also elsewhere on the board
POT_GRAIN_C: U603.12 (X3); also elsewhere on the board
POT_GRAIN_D: U604.12 (X3); also elsewhere on the board
POT_PITCH_A: U601.13 (X0); also elsewhere on the board
POT_PITCH_B: U602.13 (X0); also elsewhere on the board
POT_PITCH_C: U603.13 (X0); also elsewhere on the board
POT_PITCH_D: U604.13 (X0); also elsewhere on the board
POT_VOL_A: U601.14 (X1); also elsewhere on the board
POT_VOL_B: U602.14 (X1); also elsewhere on the board
POT_VOL_C: U603.14 (X1); also elsewhere on the board
POT_VOL_D: U604.14 (X1); also elsewhere on the board
POT_WARBLE_A: U601.1 (X4); also elsewhere on the board
POT_WARBLE_B: U602.1 (X4); also elsewhere on the board
POT_WARBLE_C: U603.1 (X4); also elsewhere on the board
POT_WARBLE_D: U604.1 (X4); also elsewhere on the board
SR_CLK: U605.2 (CP), U606.2 (CP); also elsewhere on the board
SR_MISO: U606.9 (Q7); also elsewhere on the board
SR_NLOAD: U605.1 (~PL), U606.1 (~PL); also elsewhere on the board
VOLUME_A: U601.2 (X6); also elsewhere on the board
VOLUME_B: U602.2 (X6); also elsewhere on the board
VOLUME_C: U603.2 (X6); also elsewhere on the board
VOLUME_D: U604.2 (X6); also elsewhere on the board
